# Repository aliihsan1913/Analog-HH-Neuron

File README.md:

# Analog Hardware Simulation of the Hodgkin-Huxley Neuron Model

## 1. Project Overview and Purpose
This repository contains the design, simulation, and manufacturing files for an analog computational hardware that physically models the Hodgkin-Huxley (HH) biological neuron. The primary objective is to transition neuro-biophysical concepts from theoretical mathematics into a tangible engineering prototype.

Instead of utilizing microprocessors or algorithmic software to approximate the differential equations, this circuit solves the time and voltage-dependent variables ($V, m, h, n$) in real-time using the inherent physical properties of electrons, capacitors, and non-linear analog multipliers. 

## 2. Biological Reference and Parameter Extraction
The electronic component values in this design are strictly derived from the morphological data of a real biological cell, utilizing foundational physics principles rather than hypothetical values.

* **Reference Neuron:** 1-10-8 (Rat, Neocortex)
* **Soma Surface Area:** 1147.99 µm² ($A \approx 1.15 \times 10^{-5}\ cm^{2}$)
* **Data Source:** NeuroMorpho Database

By multiplying the universal specific membrane capacitance ($1\ \mu F / cm^{2}$) and specific channel conductances by the actual surface area of the 1-10-8 neuron, the following hardware parameters were calculated and implemented in the circuit:
* **Soma Membrane Capacitance:** $\approx 11.5\ pF$
* **Sodium (Na) Channel Resistance:** $\approx 724\ k\Omega$
* **Potassium (K) Channel Resistance:** $\approx 2.41\ M\Omega$

## 3. Hardware Architecture
The system is designed on a 2-layer Printed Circuit Board (PCB) using KiCad, featuring an unbroken ground plane on the bottom layer to ensure signal integrity for the analog pathways. Trace widths are constrained to 0.25 mm with 0.20 mm clearances to accommodate the dense IC placement.

The architecture is divided into three core functional blocks:
* **Soma:** Represented by the central capacitor. The accumulation and discharge of charge on this component physically represent the resting potential and action potentials (spikes).
* **Voltage-Controlled Channels:** Built using TL072 operational amplifiers (acting as integrators for gating variables) and MPY634 precision analog multipliers. The multipliers physically execute the non-linear conductance equations (e.g., $m^3h$ for Na and $n^4$ for K).
* **Stimulus (STIM) and Threshold (THRESH):** External input ports for injecting nanoampere-level synaptic currents and a leakage resistor network to maintain the resting potential at approximately -65 mV.

## 4. Simulation and Ground Truth
Prior to hardware manufacturing, the extracted parameters were simulated in two distinct environments to verify the mathematical model against the electronic implementation.

### Mathematical Ground Truth (Python/SciPy)
The standard HH differential equations were solved using numerical integration to establish the baseline biological response. Under a 0.2 nA stimulus, the mathematical model exhibits precise spiking behavior.

### Analog Circuit Simulation (LTspice)
The physical hardware schematic was simulated in LTspice. The resulting transient analysis waveforms confirm that the analog components successfully replicate the action potentials, matching the mathematical ground truth and proving the viability of the physical circuit.

## 5. Repository Structure
* `/hardware`: Contains KiCad PCB design files and LTspice simulation models.
* `/simulation`: Contains the Python script (`hh_model.py`) for the numerical ground truth.
* `/images`: Renderings and plots used in this documentation.
* `1-10-8_Neuromorpho.md`: Detailed mathematical proofs and parameter conversion calculations.

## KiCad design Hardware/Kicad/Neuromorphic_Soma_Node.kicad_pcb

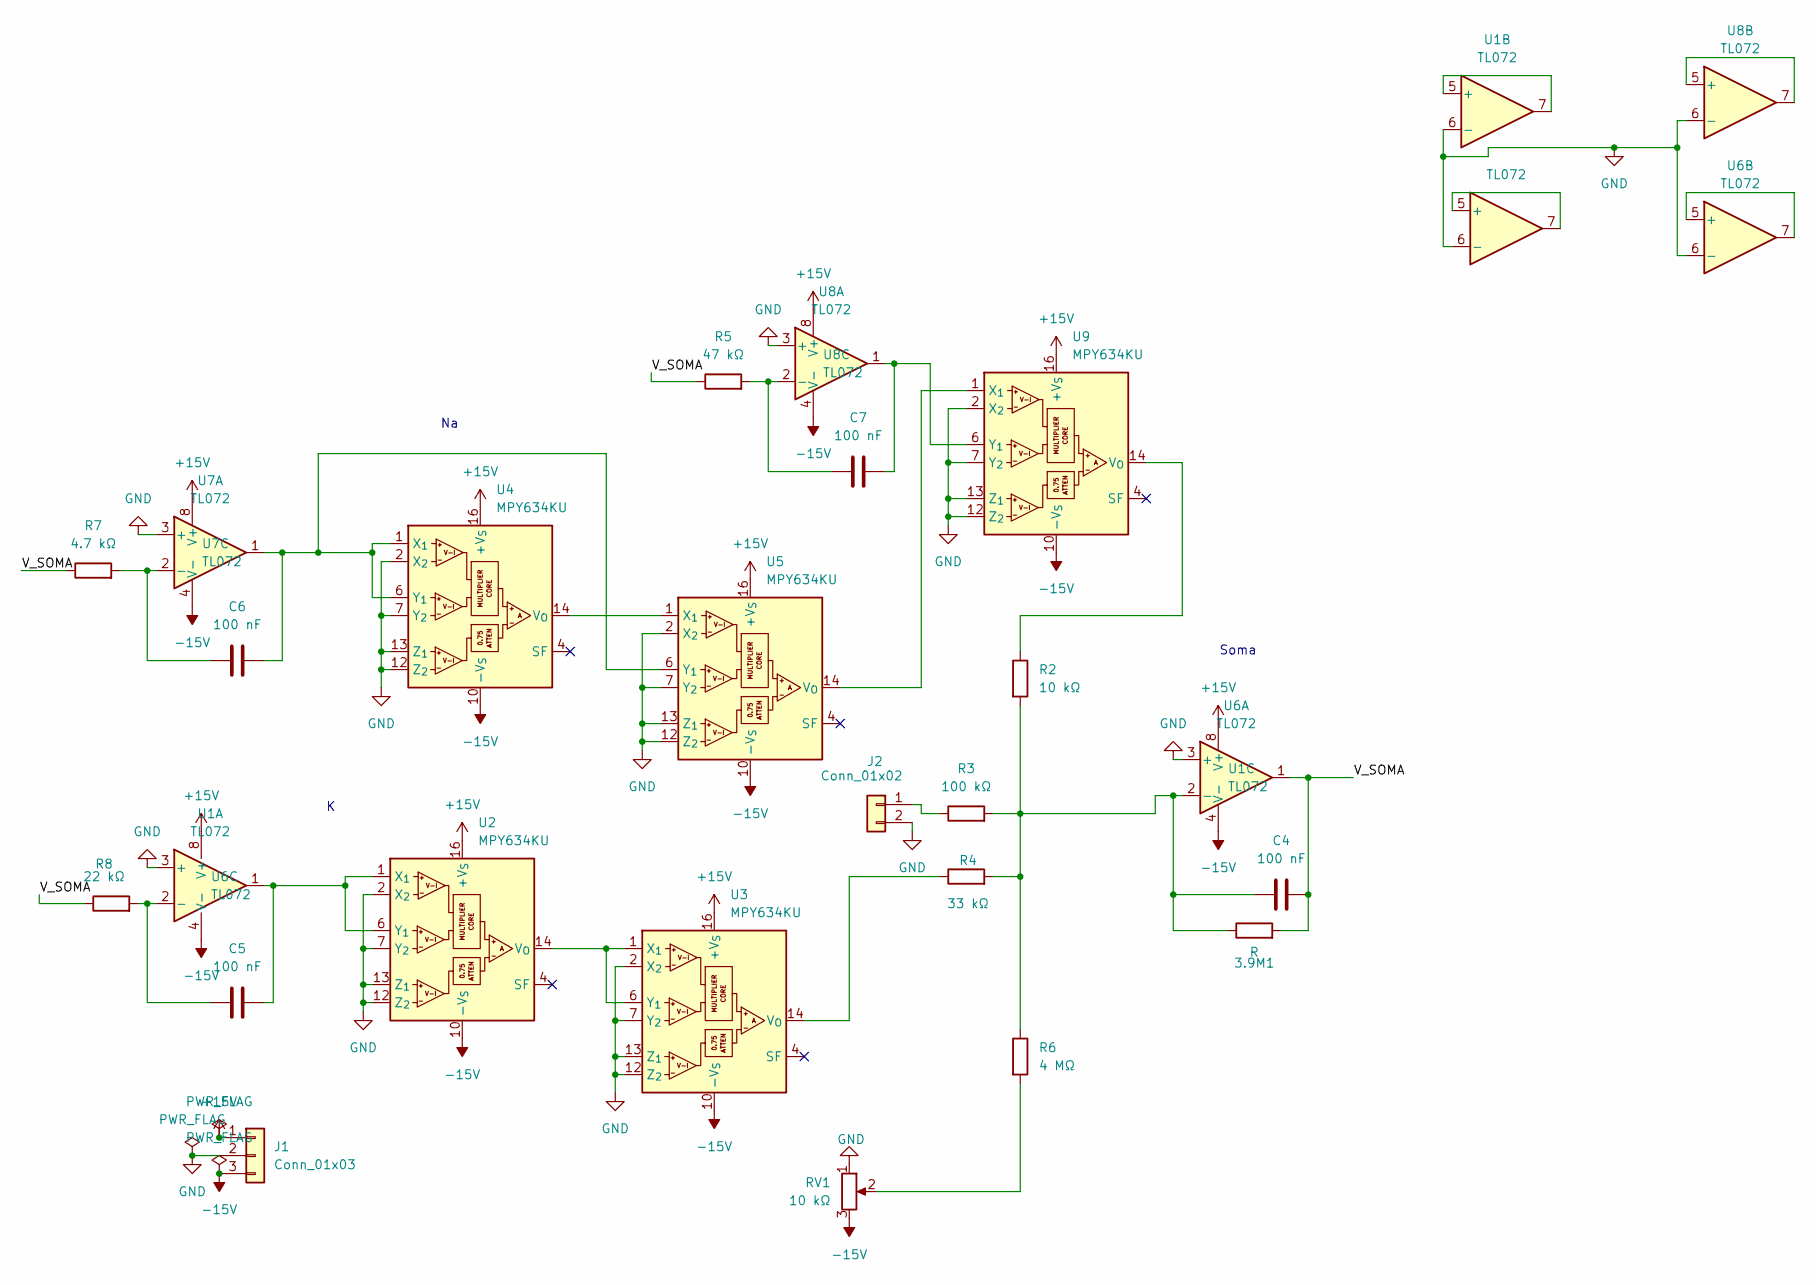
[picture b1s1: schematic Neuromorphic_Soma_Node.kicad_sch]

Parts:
3.9M1: R; R_0805_2012Metric
C4, C5, C6, C7: 100 nF; C_0805_2012Metric
J1: Conn_01x03; PinHeader_1x03_P2.54mm_Horizontal
J2: Conn_01x02; PinHeader_1x02_P2.54mm_Horizontal
R2: 10 kΩ; R_0805_2012Metric
R3: 100 kΩ; R_0805_2012Metric
R4: 33 kΩ; R_0805_2012Metric
R5: 47 kΩ; R_0805_2012Metric
R6: 4 MΩ; R_0805_2012Metric
R7: 4.7 kΩ; R_0805_2012Metric
R8: 22 kΩ; R_0805_2012Metric
RV1: 10 kΩ; Potentiometer_Bourns_TC33X_Vertical
U1, U6, U7, U8: TL072; SOIC-8-1EP_3.9x4.9mm_P1.27mm_EP2.62x3.51mm
U2, U3, U4, U5, U9: MPY634KU; SOIC-16W_7.5x10.3mm_P1.27mm

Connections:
+15V: J1.1, U1.8 (V+), U2.16 (+V_{S}), U3.16 (+V_{S}), U4.16 (+V_{S}), U5.16 (+V_{S}), U6.8 (V+), U7.8 (V+), U8.8 (V+), U9.16 (+V_{S})
-15V: J1.3, RV1.3, U1.4 (V-), U2.10 (-V_{S}), U3.10 (-V_{S}), U4.10 (-V_{S}), U5.10 (-V_{S}), U6.4 (V-), U7.4 (V-), U8.4 (V-), U9.10 (-V_{S})
/V_SOMA: 3.9M1.2, C4.2, R5.1, R7.1, R8.1, U6.1
GND: J1.2, J2.2, RV1.1, U1.3 (+), U1.6 (-), U2.2 (X_{2}), U2.7 (Y_{2}), U2.12 (Z_{2}), U2.13 (Z_{1}), U3.2 (X_{2}), U3.7 (Y_{2}), U3.12 (Z_{2}), U3.13 (Z_{1}), U4.2 (X_{2}), U4.7 (Y_{2}), U4.12 (Z_{2}), U4.13 (Z_{1}), U5.2 (X_{2}), U5.7 (Y_{2}), U5.12 (Z_{2}), U5.13 (Z_{1}), U6.3 (+), U6.6 (-), U7.3 (+), U7.6 (-), U8.3 (+), U8.6 (-), U9.2 (X_{2}), U9.7 (Y_{2}), U9.12 (Z_{2}), U9.13 (Z_{1})
unnamed: J2.1, R3.1
unnamed: R6.2, RV1.2
unnamed: C5.1, R8.2, U1.2 (-)
unnamed: U1.5 (+), U1.7
unnamed: U2.14 (V_{O}), U3.1 (X_{1}), U3.6 (Y_{1})
unnamed: C5.2, U1.1, U2.1 (X_{1}), U2.6 (Y_{1})
unnamed: R4.1, U3.14 (V_{O})
unnamed: U4.14 (V_{O}), U5.1 (X_{1})
unnamed: C6.2, U4.1 (X_{1}), U4.6 (Y_{1}), U5.6 (Y_{1}), U7.1
unnamed: U5.14 (V_{O}), U9.1 (X_{1})
unnamed: 3.9M1.1, C4.1, R2.2, R3.2, R4.2, R6.1, U6.2 (-)
unnamed: U6.5 (+), U6.7
unnamed: C6.1, R7.2, U7.2 (-)
unnamed: U7.5 (+), U7.7
unnamed: C7.1, R5.2, U8.2 (-)
unnamed: U8.5 (+), U8.7
unnamed: R2.1, U9.14 (V_{O})
unnamed: C7.2, U8.1, U9.6 (Y_{1})

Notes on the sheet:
Soma

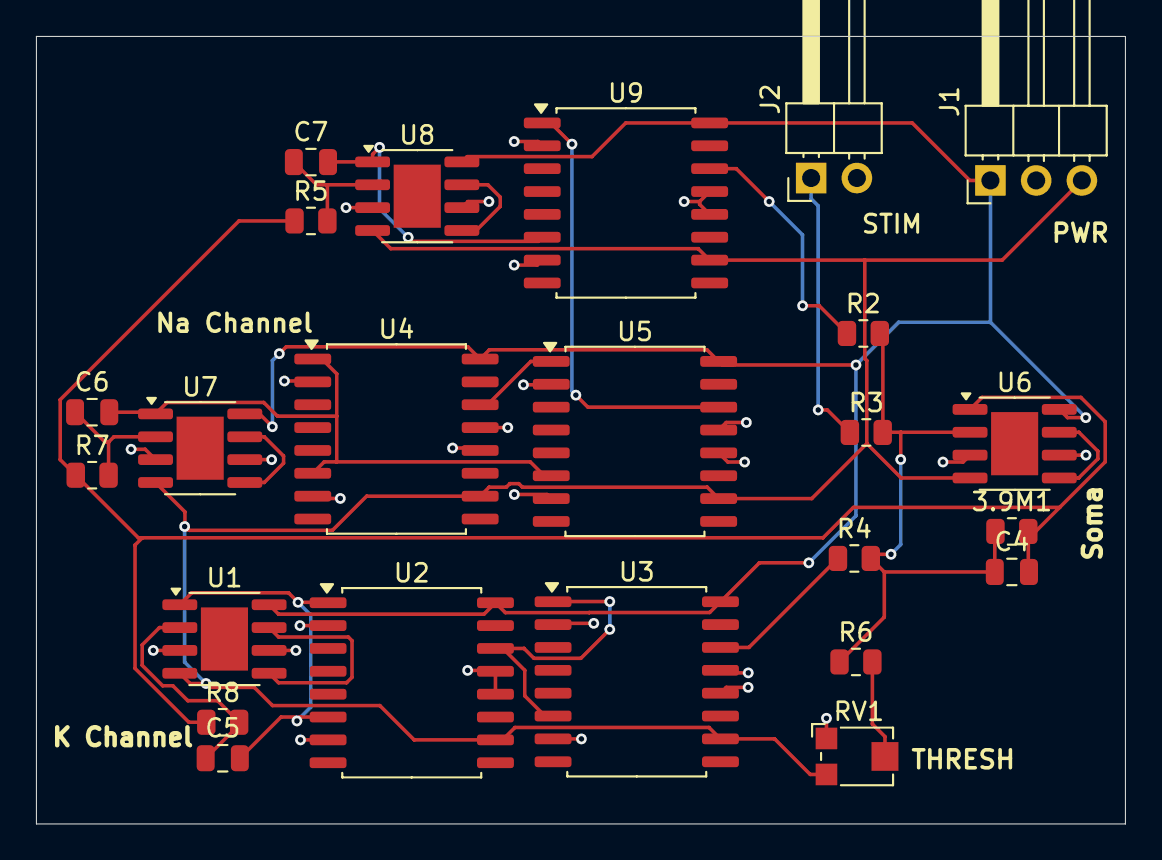
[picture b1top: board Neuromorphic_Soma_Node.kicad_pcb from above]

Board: 2 copper layers, 60.5 x 43.8 mm, 24 parts (0 on the bottom side), 22 nets.
